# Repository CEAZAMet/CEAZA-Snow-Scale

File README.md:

# CEAZA-Snow-Scale

CEAZA Snow Scale is a board designed to connect 4 load cells for the purpose of measuring snow weight in the Andes mountain range, Chile. In its v1.3.1 version, it is compatible with the protocol RS485. 

## Hardware Description

The electronic board uses an ATMEGA328P microcontroller, where the peripherals are connected to this unit. For measuring the deformation of the four load cells, two HX711 24-bit Analog-to-Digital Converter ICs are used. The RS485 communication protocol was selected for the CEAZA Snow Scale due to its long-range capability, using the SP3485EN IC as a driver. Due to the hardware's sensitivity to temperature, the DS18B20 sensor in its TO-92 package format is used for temperature measurement. 

The board has six JST connectors. Four of these are for connecting the load cells. One of them is for powering the board and for communication with other devices (via RS485). The last one is used to extend power and enable a daisy-chain topology for the RS485 protocol.

The board has two LEDs to indicate communication status with other devices, as well as a reset button for the microcontroller.

#### Schematic

#### BOM

The Bill of Materials (BOM) is located in the hardware folder [link](01.Hardware/02.BOM/BOM_CEAZA_SNOW_SCALE_V1.3.xls). This file contains the part IDs specific to the manufacturer JLCPCB, where version 1.3.1 of the board was fabricated, from there is possible to find other options for the components.

### LICENSES

<table>
  <tr>
    <td>
      
    </td>
    <td>
      
    </td>
  </tr>
</table>

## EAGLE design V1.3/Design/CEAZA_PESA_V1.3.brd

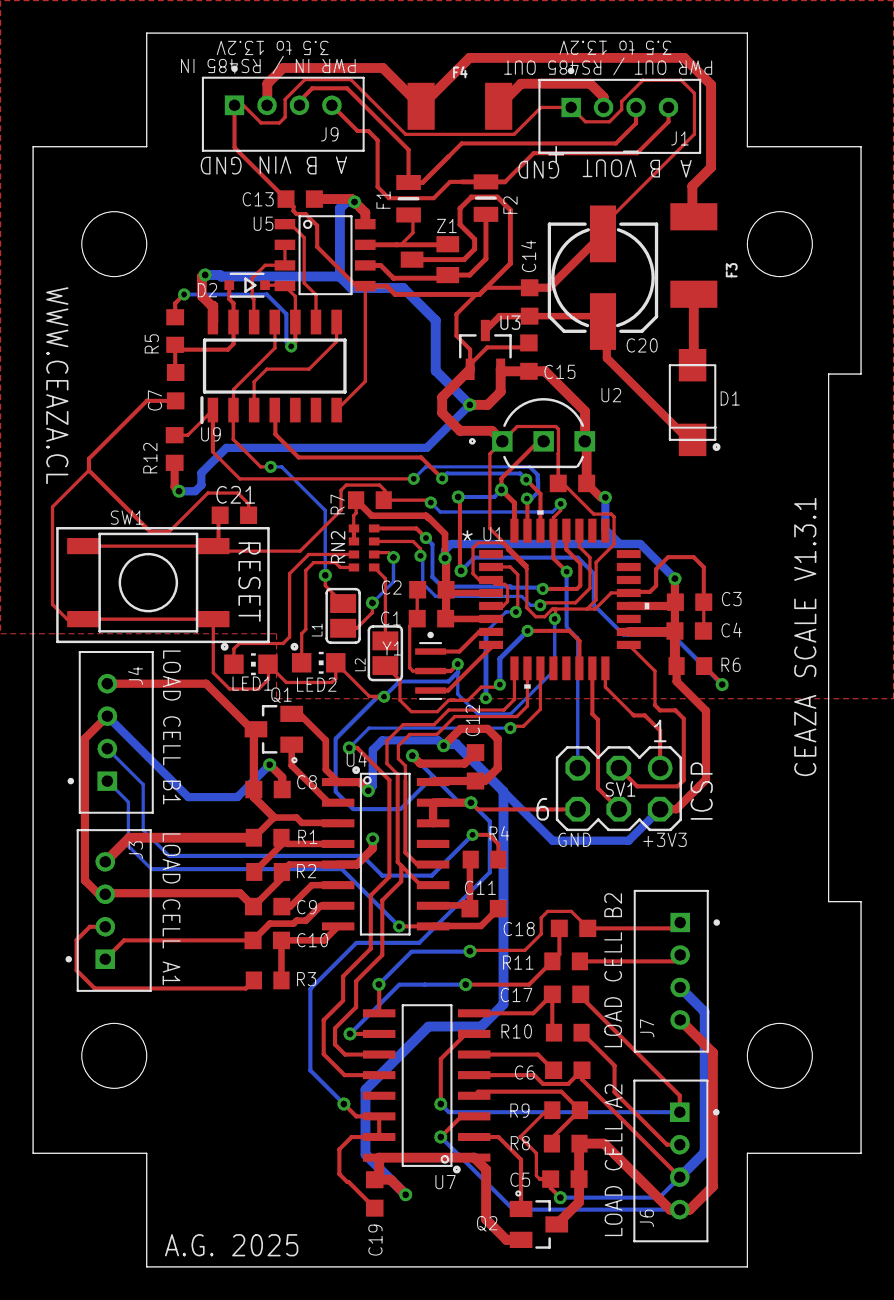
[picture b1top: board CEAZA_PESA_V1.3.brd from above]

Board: 2 copper layers, 51.0 x 76.0 mm, 63 parts (0 on the bottom side), 57 nets.

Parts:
C1, C2, C3, C4, C10, C11, C13, C16, C17, C18, C21: 100nF; C0603K
C5, C6, C8, C9, C12, C14, C15, C19: 1uF; C0603K
C7: 33pF; C0603K
C20: 47uF; 153CLV-0605
D1: SMA-SS34
D2: SOD323-R
F1, F2: FUSC2114X100N
F3, F4: 24V/500mA; 1812
J1, J9: JST_B4B-PH-K-S(LF)(SN)
J3, J4, J6, J7: B4B-PH-K-S(LF)(SN); JST_B4B-PH-K-S(LF)(SN)
L1, L2: SJ
LED1: Red; CHIP-LED0805
LED2: Green; CHIP-LED0805
Q1, Q2: MMBT3906LT1G; SOT23
R1, R8: 20K; R0603
R2, R9: 8.2K; R0603
R3, R4, R10, R11: 1.2K; R0603
R5: 56k; R0603
R6: 4.7k; R0603
R7: 100k; R0603
R12: 1K; R0603
RN2: 1k; 0603-ARV
SV1: MA03-2
SW1: SW_KH-6X6X5H-STM
U1: ATMEGA328P-AUR; 32A
U2: DS18B20; 21-0248A_MXM
U3: MCP1702T-3302E/CB; SOT95P255X145-3N
U4, U7: HX711
U5: SP3485EN-L/TR
U9: SN74HC04DR; SOIC127P600X175-14N
Y1: CSTNE8M00G55A000R0; OSC_CSTNE8M00G55A000R0
Z1: PSM712-LF-T7; SOT23

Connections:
1Y-5A: L1.1, U9.2, U9.11
4Y-2A: U9.3, U9.8
6A: C7.1, D2.A, R5.1, U9.13
+3V3: C1.1, C2.1, C3.1, C4.1, C12.1, C13.1, C15.1, C16.1, C19.1, Q1.2, Q2.2, R6.2, R7.2, R12.2, RN2.5, RN2.6, SV1.2, U1.4, U1.6, U1.18, U1.20, U2.3, U3.2, U4.1, U4.16, U5.8, U7.1, U7.16, U9.14
A+1: J3.2, R3.2
A+2: J6.2, R10.2
A-1: C10.1, J3.1, U4.7
A-2: C17.1, J6.1, U7.7
AGND: C8.2, C9.2, J3.3, J4.3, R2.1, U4.5
B+1: J4.2, R4.2
B+2: J7.2, R11.2
B-1: C11.1, J4.1, U4.9
B-2: C18.1, J7.1, U7.9
D2: R6.1, U1.32, U2.2
D5: U1.9, U4.11, U7.11
D6: U1.10, U4.12
D7: U1.11, U7.12
D13: L2.1, U1.14
DI: D2.C, R5.2, U5.4, U9.10
E+1: C8.1, J3.4, J4.4, Q1.3, R1.2, U4.3
E+2: C5.1, J6.4, J7.4, Q2.3, R8.2, U7.3
GND: C1.2, C2.2, C3.2, C4.2, C7.2, C12.2, C13.2, C14.2, C15.2, C16.2, C19.2, C20.-, C21.2, J1.1, J9.1, LED1.C, LED2.C, SV1.6, SW1.C, SW1.D, U1.3, U1.5, U1.21, U2.1, U3.1, U4.14, U4.15, U5.5, U7.14, U7.15, U9.7, Y1.2, Z1.3
GNDA: C5.2, C6.2, J6.3, J7.3, R9.1, U7.5
MISO: SV1.1, U1.16
MOSI: SV1.4, U1.15
unnamed: F2.1, U5.6, Z1.1
unnamed: Q1.1, U4.2
unnamed: LED1.A, RN2.7
unnamed: C9.1, U4.6
unnamed: R1.1, R2.2, U4.4
unnamed: Q2.1, U7.2
unnamed: C10.2, R3.1, U4.8
unnamed: C11.2, R4.1, U4.10
unnamed: R8.1, R9.2, U7.4
unnamed: U1.7, Y1.1
unnamed: U1.8, Y1.3
unnamed: LED2.A, RN2.8
unnamed: C6.1, U7.6
unnamed: C17.2, R10.1, U7.8
unnamed: C18.2, R11.1, U7.10
unnamed: F1.1, U5.7, Z1.2
unnamed: F4.2, J1.2
unnamed: D1.1, F3.2
unnamed: L1.2, RN2.2
unnamed: L2.2, RN2.1
NREDE: U5.2, U5.3, U9.12
RECTIFIED: C14.1, C20.+, D1.2, U3.3
RESET: C21.1, R7.1, SV1.5, SW1.A, SW1.B, U1.29
RO: U5.1, U9.9
RS485-A: F2.2, J1.4, J9.4
RS485-B: F1.2, J1.3, J9.3
RX: U1.30, U9.4
SCK: SV1.3, U1.17
SCL: RN2.4, U1.28
SDA: RN2.3, U1.27
TX: R12.1, U1.31, U9.1
VIN: F3.1, F4.1, J9.2

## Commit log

2025-05-15 dejar de rastrear description_snow_scale.txt
2025-05-15 Dejar de rastrear carpeta V1.3 y agregarlo al .gitignore
2025-05-15 licencias txt
2025-05-15 eliminar carpetas
2025-05-15 img licenses
2025-05-16 mod.readme.1
2025-05-16 readme hardware schematic
2025-05-16 Readme update
2025-05-16 Readme update txt
2025-05-16 Readme update md
2025-05-19 Readme update2
2025-05-19 Readme update3
2025-05-19 Readme update4
2025-05-19 Readme update5
2025-05-19 Readme update6
2025-05-19 Readme update9
2025-05-19 Readme update10
2025-05-19 Readme update12
2025-05-19 Readme update13
2025-05-19 Imported other repository into /other-repo-folder
2025-05-19 Rename folder from other-repo-folder to 05.Validation_Tests
2025-05-28 img oshwa a readme
2025-05-28 cambios readme3
2025-05-28 cambios readme4
2025-05-28 cambios readme6
2025-05-28 cambios readme7
2025-05-28 cambios readme8
2025-05-28 cambios readme9
2025-05-28 cambios readme10
2025-05-28 cambios readme11
2025-05-28 cambios license oshwa jpg
2025-05-28 cambios2 license oshwa jpg
2025-05-28 cambios3 license oshwa jpg
2025-05-28 cambios4 license oshwa jpg
2025-05-28 cambios5 license oshwa png
2025-05-28 cambios6 license oshwa png
2025-05-28 cambios7 license oshwa png
2025-05-28 cambios9 license oshwa png

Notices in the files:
parts and their libraries:
SparkFun-Fuses: Licensing: Creative Commons ShareAlike 4.0 International - https://creativecommons.org/licenses/by-sa/4.0
